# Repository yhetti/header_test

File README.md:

This project was created to test the feasibility of using 2 sets of SMT headers on a GreatFET neighbor.

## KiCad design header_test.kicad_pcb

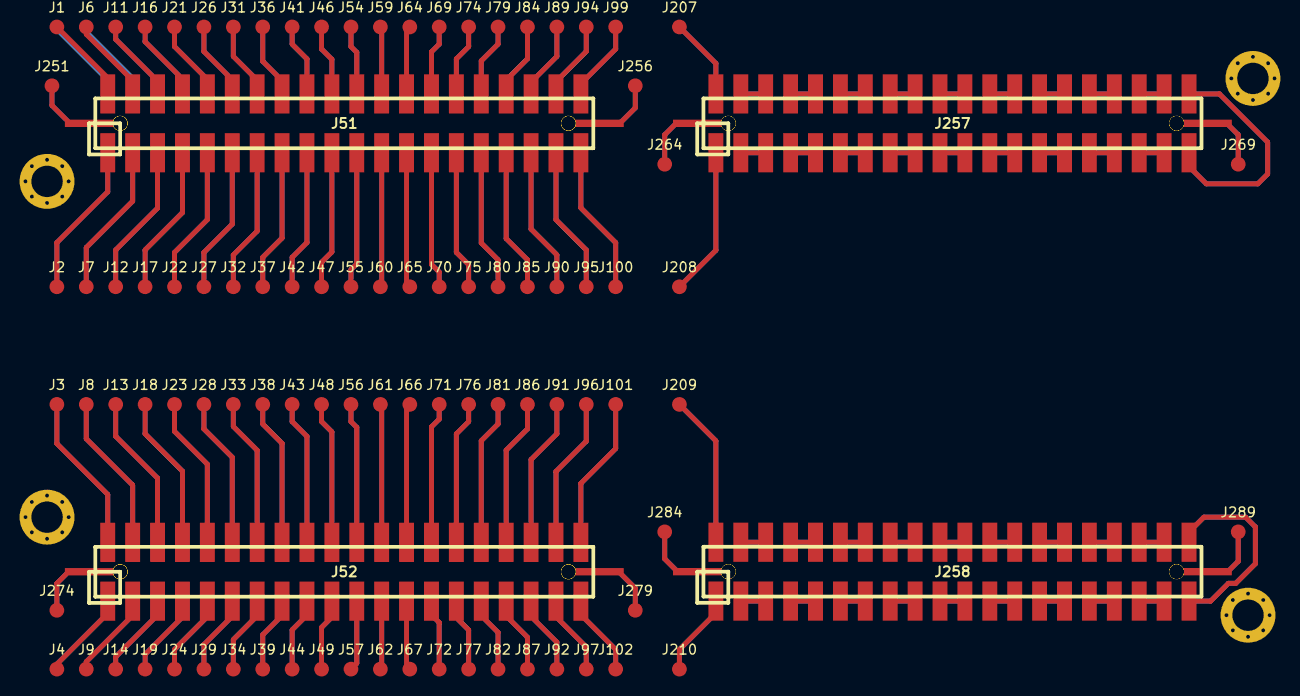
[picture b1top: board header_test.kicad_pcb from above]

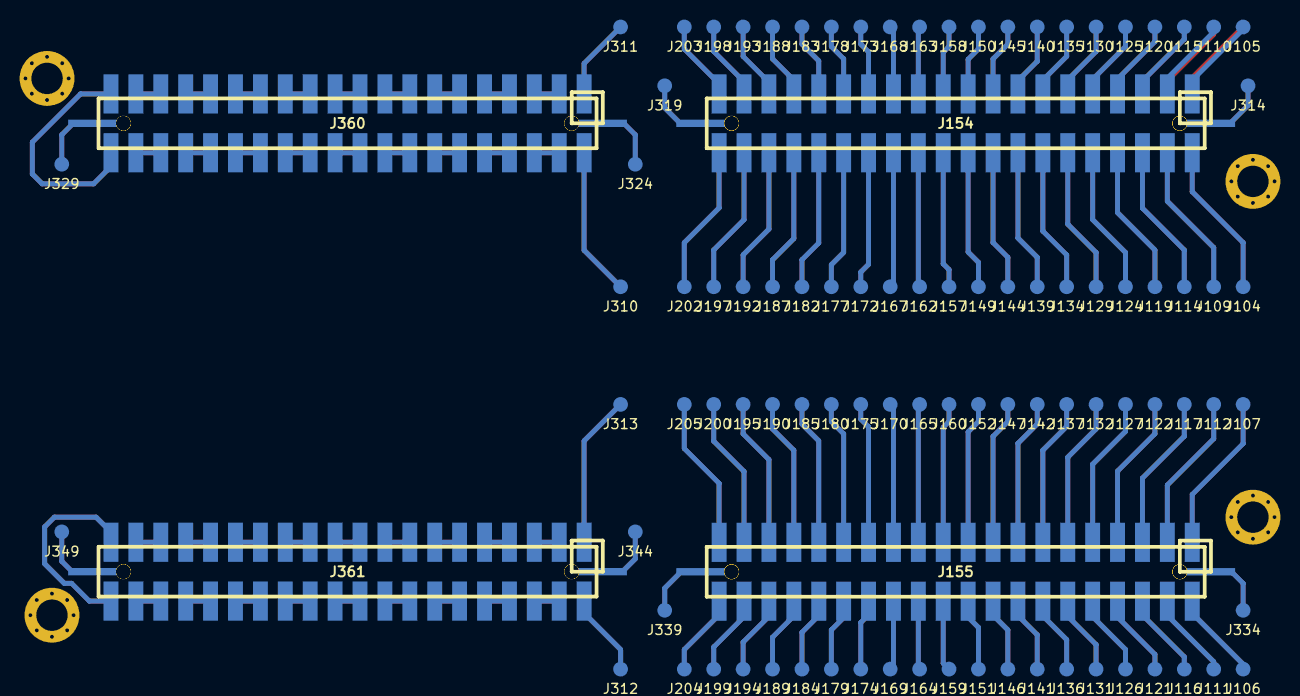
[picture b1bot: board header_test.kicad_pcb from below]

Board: 2 copper layers, 196 parts (96 on the bottom side), 52 nets.

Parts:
J1, J2, J3, J4, J6, J7, J8, J9, J11, J12, J13, J14, J16, J17, J18, J19, J21, J22, J23, J24, J26, J27, J28, J29, J31, J32, J33, J34, J36, J37, J38, J39, J41, J42, J43, J44, J46, J47, J48, J49, J54, J55, J56, J57, J59, J60, J61, J62, J64, J65, J66, J67, J69, J70, J71, J72, J74, J75, J76, J77, J79, J80, J81, J82, J84, J85, J86, J87, J89, J90, J91, J92, J94, J95, J96, J97, J99, J100, J101, J102, J104, J105, J106, J107, J109, J110, J111, J112, J114, J115, J116, J117, J119, J120, J121, J122, J124, J125, J126, J127, J129, J130, J131, J132, J134, J135, J136, J137, J139, J140, J141, J142, J144, J145, J146, J147, J149, J150, J151, J152, J157, J158, J159, J160, J162, J163, J164, J165, J167, J168, J169, J170, J172, J173, J174, J175, J177, J178, J179, J180, J182, J183, J184, J185, J187, J188, J189, J190, J192, J193, J194, J195, J197, J198, J199, J200, J202, J203, J204, J205, J207, J208, J209, J210, J251, J256, J264, J269, J274, J279, J284, J289, J310, J311, J312, J313, J314, J319, J324, J329, J334, J339, J344, J349: TEST_1P; Measurement_Point_Round-SMD-Pad_Small
J51: NEIGHBOR2_top; HEADER-2x20-LC-SMD
J52: NEIGHBOR1_top; HEADER-2x20-LC-SMD
J154: NEIGHBOR2_btm; HEADER-2x20-LC-SMD
J155: NEIGHBOR1_btm; HEADER-2x20-LC-SMD
J257: NEIGHBOR2_top_A; HEADER-2x20-LC-SMD-2
J258: NEIGHBOR1_top_A; HEADER-2x20-LC-SMD-2
J360: NEIGHBOR2_btm_A; HEADER-2x20-LC-SMD-2
J361: NEIGHBOR1_btm_A; HEADER-2x20-LC-SMD-2
MH1, MH2, MH3, MH4: MOUNTING_HOLE; HOLE126MIL-COPPER

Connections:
/ADC0_0: J7.1, J12.1, J51.3, J51.5, J110.1, J115.1, J154.3, J154.5, J257.3, J257.5, J360.3, J360.5
/CLK0: J29.1, J34.1, J52.11, J52.13, J132.1, J137.1, J155.11, J155.13, J258.11, J258.13, J361.11, J361.13
/CLK2: J26.1, J31.1, J51.12, J51.14, J129.1, J134.1, J154.12, J154.14, J257.12, J257.14, J360.12, J360.14
/I2C0_SCL: J51.39, J51.40, J99.1, J100.1, J154.39, J154.40, J202.1, J203.1, J257.39, J257.40, J360.39, J360.40
/P0_0: J8.1, J13.1, J52.4, J52.6, J111.1, J116.1, J155.4, J155.6, J258.4, J258.6, J361.4, J361.6
/P1_0: J19.1, J24.1, J52.7, J52.9, J122.1, J127.1, J155.7, J155.9, J258.7, J258.9, J361.7, J361.9
/P1_1: J18.1, J23.1, J52.8, J52.10, J121.1, J126.1, J155.8, J155.10, J258.8, J258.10, J361.8, J361.10
/P1_2: J28.1, J33.1, J52.12, J52.14, J131.1, J136.1, J155.12, J155.14, J258.12, J258.14, J361.12, J361.14
/P1_3: J52.39, J52.40, J101.1, J102.1, J155.39, J155.40, J204.1, J205.1, J258.39, J258.40, J361.39, J361.40
/P1_6: J38.1, J43.1, J52.16, J52.18, J141.1, J146.1, J155.16, J155.18, J258.16, J258.18, J361.16, J361.18
/P1_7: J39.1, J44.1, J52.15, J52.17, J142.1, J147.1, J155.15, J155.17, J258.15, J258.17, J361.15, J361.17
/P1_10: J48.1, J52.20, J52.22, J56.1, J151.1, J155.20, J155.22, J159.1, J258.20, J258.22, J361.20, J361.22
/P1_12: J49.1, J52.19, J52.21, J57.1, J152.1, J155.19, J155.21, J160.1, J258.19, J258.21, J361.19, J361.21
/P1_13: J52.24, J52.26, J61.1, J66.1, J155.24, J155.26, J164.1, J169.1, J258.24, J258.26, J361.24, J361.26
/P1_14: J52.23, J52.25, J62.1, J67.1, J155.23, J155.25, J165.1, J170.1, J258.23, J258.25, J361.23, J361.25
/P1_15: J52.28, J52.30, J71.1, J76.1, J155.28, J155.30, J174.1, J179.1, J258.28, J258.30, J361.28, J361.30
/P1_17: J52.32, J52.34, J81.1, J86.1, J155.32, J155.34, J184.1, J189.1, J258.32, J258.34, J361.32, J361.34
/P1_18: J52.31, J52.33, J82.1, J87.1, J155.31, J155.33, J185.1, J190.1, J258.31, J258.33, J361.31, J361.33
/P1_19: J52.36, J52.38, J91.1, J96.1, J155.36, J155.38, J194.1, J199.1, J258.36, J258.38, J361.36, J361.38
/P1_20: J52.35, J52.37, J92.1, J97.1, J155.35, J155.37, J195.1, J200.1, J258.35, J258.37, J361.35, J361.37
/P2_1: J51.35, J51.37, J90.1, J95.1, J154.35, J154.37, J193.1, J198.1, J257.35, J257.37, J360.35, J360.37
/P2_2: J51.31, J51.33, J80.1, J85.1, J154.31, J154.33, J183.1, J188.1, J257.31, J257.33, J360.31, J360.33
/P2_3: J46.1, J51.20, J51.22, J54.1, J149.1, J154.20, J154.22, J157.1, J257.20, J257.22, J360.20, J360.22
/P2_4: J47.1, J51.19, J51.21, J55.1, J150.1, J154.19, J154.21, J158.1, J257.19, J257.21, J360.19, J360.21
/P2_5: J36.1, J41.1, J51.16, J51.18, J139.1, J144.1, J154.16, J154.18, J257.16, J257.18, J360.16, J360.18
/P2_6: J37.1, J42.1, J51.15, J51.17, J140.1, J145.1, J154.15, J154.17, J257.15, J257.17, J360.15, J360.17
/P2_8: J27.1, J32.1, J51.11, J51.13, J130.1, J135.1, J154.11, J154.13, J257.11, J257.13, J360.11, J360.13
/P3_0: J51.24, J51.26, J59.1, J64.1, J154.24, J154.26, J162.1, J167.1, J257.24, J257.26, J360.24, J360.26
/P3_3: J51.32, J51.34, J79.1, J84.1, J154.32, J154.34, J182.1, J187.1, J257.32, J257.34, J360.32, J360.34
/P3_4: J51.28, J51.30, J69.1, J74.1, J154.28, J154.30, J172.1, J177.1, J257.28, J257.30, J360.28, J360.30
/P3_6: J51.36, J51.38, J89.1, J94.1, J154.36, J154.38, J192.1, J197.1, J257.36, J257.38, J360.36, J360.38
/P4_0: J6.1, J11.1, J51.4, J51.6, J109.1, J114.1, J154.4, J154.6, J257.4, J257.6, J360.4, J360.6
/P4_2: J16.1, J21.1, J51.8, J51.10, J119.1, J124.1, J154.8, J154.10, J257.8, J257.10, J360.8, J360.10
/P4_3: J17.1, J22.1, J51.7, J51.9, J120.1, J125.1, J154.7, J154.9, J257.7, J257.9, J360.7, J360.9
/P4_10: J9.1, J14.1, J52.3, J52.5, J112.1, J117.1, J155.3, J155.5, J258.3, J258.5, J361.3, J361.5
/P5_6: J52.27, J52.29, J72.1, J77.1, J155.27, J155.29, J175.1, J180.1, J258.27, J258.29, J361.27, J361.29
/P6_8: J51.27, J51.29, J70.1, J75.1, J154.27, J154.29, J173.1, J178.1, J257.27, J257.29, J360.27, J360.29
/P7_1: J51.23, J51.25, J60.1, J65.1, J154.23, J154.25, J163.1, J168.1, J257.23, J257.25, J360.23, J360.25
/VBUS: J1.1, J51.2, J104.1, J154.2, J207.1, J257.2, J310.1, J360.2
GND: J51.0, J52.0, J251.0, J256.0, J257.0, J258.0, J264.0, J269.0, J274.0, J279.0, J284.0, J289.0, J324.0, J329.0, J344.0, J349.0, J360.0, J361.0, MH1.1, MH2.1, MH3.1, MH4.1
unnamed: J2.1, J51.1
unnamed: J3.1, J52.2
unnamed: J4.1, J52.1
unnamed: J105.1, J154.1
unnamed: J106.1, J155.2
unnamed: J107.1, J155.1
unnamed: J208.1, J257.1
unnamed: J209.1, J258.2
unnamed: J210.1, J258.1
unnamed: J311.1, J360.1
unnamed: J312.1, J361.2
unnamed: J313.1, J361.1

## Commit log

2018-01-15 Created header_test repo
